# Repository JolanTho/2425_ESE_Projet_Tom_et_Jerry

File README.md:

# 2425_ESE_Tom&Jerry

## Sommaire
- [Présentation](#présentation)
- [Mécanique](#1-mécanique)
- [Électronique](#2-électronique)
- [Informatique](#3-informatique)
- [Stratégies](#4-stratégies)
- [Installation](#installation)
- [Contribution](#contribution-)
- [Auteurs et Contact](#auteurs-)

---

## Présentation

>Bienvenue sur le dépôt GitHub de **Tom&Jerry**. Ce projet a pour but de développer un robot autonome qui sur un plan plat joue à chat. Le plan est sans rebord, les matchs de 60secondes et le robot change de rôle (Chat/Souris) lors des contacts avec le(s) autre(s) robot(s).

>Ce projet est organisé en trois sous-domaines principaux :
>* **Mécanique** : Conception et fabrication des structures et composants mécaniques.
>* **Électronique** : Conception des circuits électroniques et sélection des composants.
>* **Informatique** : Développement du logiciel et de l'algorithme pour le contrôle du système.
>* **Stratégies** : Focus sur les stratégies mises en place pour s'échapper ou capturer.

---

## Détails du Projet

### 1. Mécanique
>Cette section est dédiée à la conception et à la fabrication des parties mécaniques du projet. 

#### Description :
- **Modélisation CAO** : Les pièces du projet ont été modélisées en utilisant **OnShape**.
- **Matériaux** : Les matériaux utilisés incluent **Plastique PLA, ...**.
- **Assemblage** : Le système est assemblé à l’aide de **(ex. vis, écrous, etc.)** et monté selon les plans fournis dans le dossier **/mechanical_drawings**.

#### Fichiers et Dossiers :
>* **/mechanical_drawings/** : Contient les fichiers CAO et les plans techniques.
>* **/materials_list.txt** : Liste des matériaux et composants utilisés.

---

### 2. Électronique
>Cette partie couvre la conception et le développement des circuits électroniques nécessaires pour alimenter et contrôler le système.

#### Description :
>* **Schémas électroniques** : Conception des circuits avec **Kicad**.
>* **Liste des composants** : Utilisation de microcontrôleurs comme **STM32**, capteurs **TOF, Capteur fin de course, Lidar, IMU, Odom**, et actionneurs **Moteurs de roues**.
>* **PCB** : Un circuit imprimé (PCB) a été conçu pour **Alimentation & Décision du robot**.

#### Fichiers et Dossiers :
>* **electronique/Tom&Jerry_PCB/** : Projet Kicad du PCB principal.
>* **electronique/TOF_PCb/** : Projet Kicad du PCB annexe pour les TOF.
>* **[Read.me ToF](electronique/READMETom&Jerry.md)**
>* **[Read.me Tom&Jerry](electronique/READMETom&Jerry.md)**

---

### 3. Informatique
>Cette section inclut le code source et les algorithmes permettant de contrôler le système.  

#### Description :
>* **Langages utilisés** : Le logiciel a été développé en **C**.  
>* **Architecture logicielle** : L'architecture du programme suit un modèle **/programm_diagramm**.  
>* **Modules et fonctionnalités** : Le logiciel gère **(ex. les capteurs, la communication avec le microcontrôleur, les algorithmes de contrôle**.  

#### Fichiers et Dossiers :
>* **/src/** : Contient le code source du projet.  
>* **/docs/** : Documentation du code et guide d’utilisation.  
>* **/scripts/** : Scripts auxiliaires pour tester ou déployer le logiciel.  
>* **[Read.me](software/README.md)**
---

### 4. Stratégies
>Cette section inclut tout ce qu'il faut savoir sur les stratégies décidées et mis en oeuvre.  

>[!Note]
> Pour faire fonctionner le robot plusieurs stratégies peuvent être mises en place.   
> **Lorsque nous sommes souris**  
>* 1. On fait avancer le robot sur des stratégies prédéfinies et on espère ne pas tomber sur le chat.  
>* 2. On donne des trajectoires aléatoires au robot et on espère ne pas tomber sur le chat ou de la table.  
>* 3. On donne des trajectoires aléatoires en évitant le chat en priant pour ne pas tomber de la table.  
>* 4. On utilise un champ de potentiel pour se repérer et éviter le chat et les bordures.  
>  
> **Lorsque nous sommes Chat**  
>* 1. On fait avancer le robot sur des stratégies prédéfinies et on espère toucher une souris.   
>* 2. On donne des trajectoires aléatoires au robot et on espère toucher une souris sans tomber.  
>* 3. Le Lidar donne l'endroit ou on fonce a pleine balle.  
>* 4. Le lidar donne l'endroit ou on fonce a pleine balle en prenant en compte que l'objectif bouge.   

---

## Installation

### Prérequis :
>[!Important]
>* **Matériel** : La liste du matériel nécessaire ce situe dans le fichier BOM ici, ainsi que dans la partie mécanique ici.
>* **Logiciel** : Nous utilisons STM32 CubeIDE pour programmer notre microcontrolleur. De plus pour la simulation le python est utilisé. 
>* **Connaissance** : Pour comprendre plainement le projet il est nécessaire de maitriser (Kicad, STM32CubeIDE, Onshape). Avec une idée de comment marche les microcontrolleur STM32. (Un ensearque a réussi vous devriez aussi y parvenir).

---

### Instructions :

>[!Tip]
> **Pour utiliser le projet sur un robot**  

1. Cloner le dépôt : 
   ```bash
   git clone https://github.com/JolanTho/2425_ESE_Projet_Tom_et_Jerry.git
   cd projet
   
>[!Tip]
> **Pour utiliser la simulation de champs potentiel**  

1. Cloner le dépôt : 
   ```bash
   git clone https://github.com/JolanTho/2425_ESE_Projet_Tom_et_Jerry.git
   cd projet
---

## Contribution :

---

## Auteurs : 
>* Jolan Thomasset (jolan.thomasset@ensea.fr)  
>* Romain Pace   (romain.pace@ensea.fr)  
>* Rémi Weidle   (remi.weidle@ensea.fr)

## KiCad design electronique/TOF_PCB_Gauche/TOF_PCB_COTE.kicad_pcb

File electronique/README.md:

# Partie éléctronique 

## Sommaire
- [Présentation](#présentation)
- [Alimentation](#alimentation)
- [Driver Moteurs](#drivers-moteurs)
- [STM32](#stm32)
- [Peripheriques](#périphériques)
- [Peripherique Annexe](#périphériques-annexes)
- [Musique](#musique)

---

## Présentation
>Bienvenue dans la partie éléctronique du projet, dans ce dossier sont présent tous les fichiers de conception du PCB KiCad ainsi que tous les fichiers de fabrications Gerber.  
Deux fichiers sont actuellement dans le directory. Tom&Jerry_PCB pour le PCB principal et TOF_PCB pour le secondaire.   
Il est détaillé chaque composante du Schématique/PCb dans ce Read.me  

---

## Alimentation
>[!Tip]
>Pour notre robot nous utilisons plusieurs système pour gérer le circuit d'alimentation. On a entre autre un BMS ( Batterie système management ), ainsi qu'un pseudo Power Path Management. La batterie utilisée est la suivante : [here](../datasheet/Batterie.pdf)  

>[!Tip]
>Des connecteurs Pac-Man sont utilisés au niveau de la recharge de batterie afin de pouvoir déconnecter facilement le circuit de charge si il est foireux. De plus un interrupteur est ajouté pour allumer/Eteindre le robot ainsi qu'un fusible pour protéger des surcourants sur la batterie.  

**Recharge de batterie**

[Recharge](../screenshot/electronique/usbC.png)

>Pour la recharge de la batterie nous prévoyons deux connecteurs : Type-C et Bornier afin de pouvoir recharger la batterie par alimentation stabilisée de labo ainsi que par cable USB-C (Plus difficile à mettre en oeuvre) [Documentation1](../datasheet/PPM_BMS.pdf).  

>[!Note]
>Cette entrée d'energie est gérée par le **BMS [BQ25172DSGR](../datasheet/BQ25172.pdf) de TI**. Celui-ci est cablé tel quel :  
>* IN : Entrée de tension de charge de batterie. Max 0.8 A (Cf : Doc)  
>* VSET : Programme le nombre de cellule --> 6 cellules + Charge intermittente  
>* ISET : Programme le courant de charge --> 0.8A   
>* TMR : Programme le Timer de sureté --> 6Hr  
>* TS : Programme la température de sureté de charge --> Donnée constructeur    
>* OUT : Sortie de tension de charge de la batterie  
>* STAT : Sortie d'indication de l'état de charge à drain ouvert  
>* EXP : Ground (Pad thermique)  
>* GND : Ground  

[CanalP](../screenshot/electronique/canalP.png)

>On a un transistor à canal P pour bloquer la charge du circuit par batterie lorsqu'une tension vient du bornier ou de l'USB-C. De plus on ajoute des condensateur (C...) pour eviter les retours de courant dû a des freinage des roues dans la résistance et donc dans l'alimentation derrière [(Doc)](../datasheet/slua376.pdf).    

>On utilise un premier convertisseur Buck pour abaisser la tension à 5V. Celui-ci est à découpage donc plus cher mais possède un meilleur rendement et un plus faible échauffement. Cela est parfait puisqu'il alimente le lidar ainsi que tous les circuits 3.3v derrière et donc peut avoir des appels de courant assez élevé (Comme démarrage de lidar).  

>[!Note]
>**Convertisseur Buck ([MP1475](../datasheet/MP1475.pdf))**  
>* IN : Tension d'entrée  
>* BST : Bootstrap  
>* SWT : Sortie de commutation  
>* PG : Sortie de puissance  
>* VCC : LDO interne de 5v  
>* EN/SYNC : Pour les clocks externes  
>* FB : Feedback  
>* GND : Ground  

>Actuellement les données sont celle ce la doc. La seule chose réglée est le pont diviseur avec une Vref = 1.25V pour avoir une sortie de 5V en sortie.  

>Simple convertisseur linéaire qui abaisse de 5V vers 3.3V pour alimenter certains capteurs ou encore la STM32 qui n'accepte pas du 5V. L'utilisation d'un buck serai plus utile si on recherche la performance cependant un LDO est suffisant car moins couteux, plus simple à mettre en place. L'abaissement de tension est faible sur de faible courants par conséquent la dissipation thermique sera faible ce qui justifie un LDO plutôt qu'un buck.  

>[!Note]
>**Convertisseur LDO [(BU33SD5WG-TR)](../datasheet/buxxsd5wg-e.pdf)**  
>* VIN : Tension d'entrée  
>* GND : Ground  
>* STBY : StandBy --> Ici sur High il marche dés qu'il est alimenté.   
>* N. C. : No Connected pin  
>* Vout : Tension de sortie  

---

## Drivers moteurs
>Afin de pouvoir mouvoir le robot sur la table de jeu, nous utilisons des moteurs type MCC (DfRobot FIT0520). Ces moteurs possèdent des codeurs déjà sur l'arbre moteur ce qui a l'avantage de ne négliger aucun décalage entre une roue de codeur et la roue de l'arbre moteur. Cependant si jamais la roue patine ou glisse le codeur ne prendra pas en compte ce dérapage ce qui entrainera des erreurs. Il faut donc impérativement que la mécanique permette au robot de rester particulièrement stabilisé sur le sol.  

>[!Note]
>Branché sur la carte les deux moteurs auront de beaux JST-XH de 6 Pins chacun tels que :  
>* Motor - : Phase - du moteur  
>* Motor + : Phase + du moteur  
>* GND : Ground   
>* 5V : Alimentation des codeurs en 5V   
>* Codeur PH1 : Pin allant avec PH2 avec la trame du codeur pour déterminer ensuite la vitesse du robot.   
>* Codeur PH2 : Pin allant avec PH1 avec la trame du codeur pour déterminer ensuite la vitesse du robot.   

>Pour controler ces deux moteurs chaque moteur aura son driver.   

>[!Note]
>**Driver [ZXBM5210](../datasheet/ZXBM5210.pdf)**  
>* Vref : Tension de référence pour setup l'oscillator PWM du composant.   
>* VDD : Alimentation du composant en 5V   
>* VM : Tension d'alimentation des moteurs  
>* FWD : PWM pour faire avancer le robot  
>* REV : PWM pour faire reculer le robot  
>* Out 1 :  Sortie au moteur phase -  
>* Out 2 : Sortie au moteur phase +  

>[!Important]
>Il est à noter que des capa de découplage sont utilisés afin d'éviter les fluctuation de courant trop rapide sur Vref ( Car tension de référence), sur les phases du moteur afin d'éviter des signaux créneau pur. De plus la documentation suggère un système de diode afin d'éviter la réversibilité du courant vers la batterie. Celui-ci ne sera pas utilisé afin d'éviter de cramer des diodes suite à des quantités trop importantes de courant que se déchargeraient dans les diodes.   

>[!Tip]
>En plus de cela nous utilisons un composant pour mesurer le courant drainé de la batterie vers les moteurs à l'aide d'une résistance dite shunt. Ce composant permettra de nous aider à asservir pourquoi pas en courant mais aussi de protection afin d'éviter comme nous n'avons pas mis les diodes d'avoir des données sur ce qui se passe.  

>[!Note]
>**Mesureur de courant [NCS199A2RSQT2G](../datasheet/NCS199A2RSQT2G.pdf)**  
>* GND : Ground  
>* In + : Entrée + coté résistance de shunt pour capter le courant  
>* In - : Entrée - coté résistance de shunt pour capter le courant  
>* Vs : Tension d'alimentation du composant  
>* Vref : Tension de référence dont je ne sais pas à quoi elle sert (J'ai cable comme la doc)  
>* Out : Sortie du composant avec ke courant prêt à être lu par un ADC  

>Comme toute entrée de composant celui-ci ne fait pas l'impasse une capacité de découplage a été ajoutée. De plus la résistance de 1kOhm a été mise pour préparer l'entrée du courant dans l'ADC conforme à la documentation.  

---

## STM32 
>[!Important]
>Avant de développer sur la STM32 et la facon dont nous avons répartis les pins de celle-ci. Pour que celle-ci fonctionne correctement nous utiliserons un quartz externe pour cadencer la STM32 (Configuré dans l'IOC de STM32CubeIDE). 

>[!Important]
>De plus nous utilisons une connexion STLink pour le debug de la carte via PC. 

---

## Périphériques 

>[!Note]
>La carte actuelle va gérer certains capteurs. Avec ceux-ci le robot pourra (Nous l'esperons) se repérer sur la table et réaliser au mieux la stratégie mise en place. 

>[!Tip]
> Afin de détecter les bords nous avons décider de faire de la redondance. En effet nous utilisons des capteurs "Moustache" ainsi que TOF pour repérer les bords de la table et éviter que les robots tombent. L'avantage des capteurs moustache est qu'ils sont mécanique donc fiable maintenant cela demande de na pas louper son intégration sur la base roulante ce qui n'es tpas gagner. Pour cela nous pouvvons utiliser les TOF. Ceux-ci sont plus simple à positionner sur le robot et à fonctionner. Cependant l'exploitation des données est plus dure (I2C + GPIO Extender...). 

>[!Note]
>Branché sur la carte les quatre capteurs moustahce ont un JST  :  
>* 3.3V : Alimentation
>* GND : Ground  
>Ceux-ci marchent en interrupteur pas besoin de plus de chose pour lire leurs données. 

>[!Note]
>**Capteurs TOF [VL53L1X](../datasheet/VL53L1X.pdf):**   
>* AVDDVCSEL : VCSEL tension d'alimentation  
>* AVSSVCSEL : VCSEL Ground    
>* GND1 - GND4 : Ground  
>* XShut: Pin pour shutdown le composant. celui-ci est actif sur un signal Bas  
>* GPIO1 : GPIO pour gérer les interruptions  
>* DNC : A ne pas connecter (Doit être floating)  
>* SDA : Serial data bus
>* SCL : Serial clock bus
>* AVDD : Tension d'alim du composant
>Ceux-ci sont sur les cartes fournient avec produit par STM32. 

>[!Note]
>En plus de la détection de bord avec les TOF et les capteurs "Moustache", le robot aura un IMU pour faire de la fusion de donnée (Rédigé en septembre ca ne sera pas traité pas assez de temps) ainsi que de vérifier si un robot nous touche. De plus il y aura un lidar pour détecter les robots sur la table et foncer sur eux. 

>[!Note]
>**Capteurs TOF [YDLidar X2](../datasheet/YDLIDARX2.pdf):**    
>* M_CTR : Entrée de la PWM du moteur du Lidar    
>* TX : Sortie UART avec les données du LIDAR      
>* GND : Ground    
>* VCC : Tension d'alimentation du lidar (5v)  

>[!Note]
>**IMU [ADXL343](../datasheet/ADXL343.pdf):**   
>* Vs : Tension d'alimentation du composant   
>* GND : Ground   
>* VDD : Tension d'alimentation de l'interface digitale  
>* SDA : Serial data bus  
>* SCL : Serial clock bus  
>* SDO : I2C adresse  
>* NC : A garder non connecte  
>* Int1 - Int2 : Pin d'interruption   
>* CS : Chip Select

---

## Périphériques Annexes 
>Deux composants non imposés ont été utilisés en plus de ceux imposés afin de pouvoir tout connecter à la STM32. Suite à la solution technique des TOF employé le nombre de GPIO recquis a quelque peu explosé surpassant la capacité de la STM. par conséquent un GPIO Extender est utilisé pour ajouter des GPIO afin de couper et utiliser les TOF lorsque nous en avons besoin.   

>[!Note]
>**GPIO Extender [TCA9555RTWR](../datasheet/TCA9555.pdf)**  
>* A0 : Adress Input 0  
>* A1 : Adress Input 1  
>* A2 : Adress Input 2  
>* GND : Ground   
>* P00 à P17 : P/port I/O connecte comme Input au démarrage.   
>* SCL : Serial clock bus  
>* SDA : Serial data bus  
>* VCC : Tension d'alimentation du composant  
>* INT : Permet de donner des interruptions avec une Pull-Up resistance.   

>[!Tip]
>En plus de ce composant nous avons utilisé un petit composant pour traiter nos leds. En effet en comptant 4 de débugs, robot allumé, chat/souris,... Nous nous sommes sentis à l'étroit et avons décidé de rajouter un composant qui drive 4 RGB. Cela sera parfait pour débug et montrer les informations nécessaires.  

>[!Note]
>**RGB LED Driver [LP5812CDSDR](../datasheet/LP5812.pdf)**  
>* VCC : Tension d'alimentation du composant  
>* GND : Ground  
>* SYNC : Synchro du composant sur GND (C'est la doc je sais pas pk)  
>* SCL : Serial clock bus  
>* SDA : Serial data bus   
>* OUT0 - OUT3 : Sorties vers les LED   

>Pour ce composant nous verrons pour le faire marcher en temps voulu avec le SPI pour allumer nos LEDS. Celles-ci sont cablés comme décrit dans la documentation.   

---

## Musique 
>Ayant dans notre groupe notre jolan nationnal, le projet ne pouvait être correctement réalisé sans l'ajout de bout de musique sur le robot. Pour se faire les sorties DAC de la STM32 dédiées seront utilisées. Ce signal audio sera amplifié par un amplificateur de Classe D puis va être envoyé dans des hauts parleurs.   

>[!Note]
>**Ampli de Classe D [PAM8302AAY](../datasheet/PAM8302A.pdf)**  
>* IN + : Entrée DAC  +  
>* IN - : Entrée DAC  -   
>* SD : Doit rester sur HIGh pour éviter qu'il soit shutdown (donc relié à 3.3v)  
>* VDD : Alimentation du composant  
>* OUT + : Sortie + du haut parleur   
>* OUT - : Sortie - du haut parleur  

>[!Important]
>Les deux capacité de découplage ainsi que les deux ferrites sont celles conforme à la documentation afin de réduire les interférence electromagnétique à partir de 1MHz et au dela. Ceci est parfait puisque ce composant est à coté de composant sensible comme la STM...  

## Auteurs : 
>* Jolan Thomasset (jolan.thomasset@ensea.fr)  
>* Romain Pace   (romain.pace@ensea.fr)  
>* Rémi Weidle   (remi.weidle@ensea.fr)

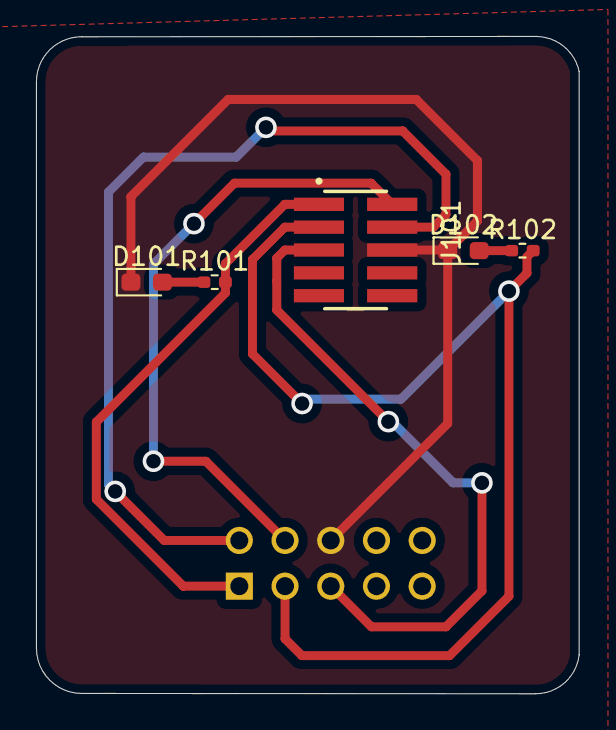
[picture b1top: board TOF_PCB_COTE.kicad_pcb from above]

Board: 2 copper layers, 30.2 x 36.5 mm, 6 parts (1 on the bottom side), 8 nets.

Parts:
D101, D102: LED; LED_0603_1608Metric_Pad1.05x0.95mm_HandSolder
J101: FTSH-105-01-F-DV-P-TR; SAMTEC_FTSH-105-01-F-DV-P-TR
R101, R102: 3.3k; R_0402_1005Metric_Pad0.72x0.64mm_HandSolder
U101: VL53L1X-SATEL; MODULE_VL53L1X-SATEL

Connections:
+5V: J101.05, U101.5 (VDD)
/I2C_MAIN_SCL: J101.04, U101.2 (SCL_I)
/I2C_MAIN_SDA: J101.02, U101.4 (SDA_I)
/TOF_GPIO1: J101.01, R101.2, U101.1 (INT_I)
/TOF_XSHUT: J101.03, R102.2, U101.3 (XSDN_I)
GND: D101.1 (K), D102.1 (K), J101.06, U101.6 (GND)
unnamed: D101.2 (A), R101.1
unnamed: D102.2 (A), R102.1

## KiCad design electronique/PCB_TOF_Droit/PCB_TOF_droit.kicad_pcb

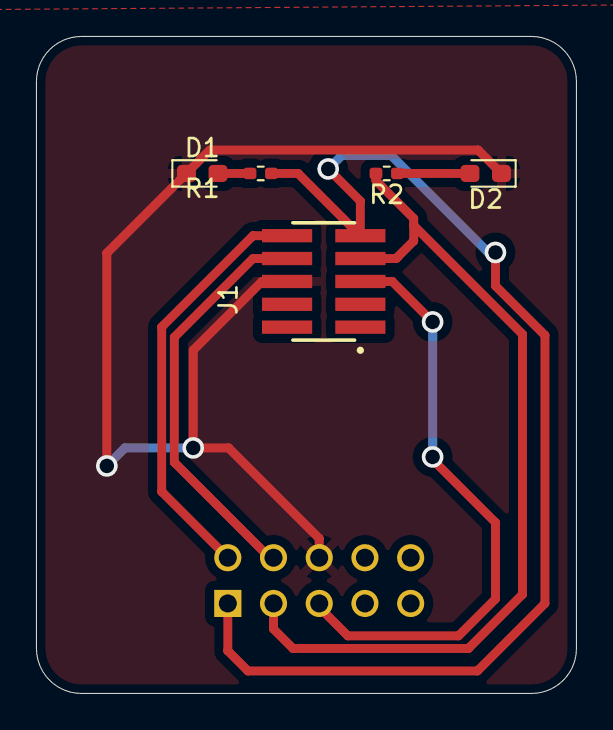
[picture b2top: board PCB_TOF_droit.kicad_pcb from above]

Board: 2 copper layers, 30.0 x 36.5 mm, 6 parts (1 on the bottom side), 8 nets.

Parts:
D1, D2: LED; LED_0603_1608Metric_Pad1.05x0.95mm_HandSolder
J1: FTSH-105-01-F-DV-P-TR; SAMTEC_FTSH-105-01-F-DV-P-TR
R1, R2: 3.3k; R_0402_1005Metric_Pad0.72x0.64mm_HandSolder
U1: VL53L1X-SATEL; MODULE_VL53L1X-SATEL

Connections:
+5V: J1.05, U1.5 (VDD)
/I2C_SCL: J1.10, U1.2 (SCL_I)
/I2C_SDA: J1.08, U1.4 (SDA_I)
/TOF_GPIO: J1.09, R1.2, U1.1 (INT_I)
/TOF_XSHUT: J1.07, R2.2, U1.3 (XSDN_I)
GND: D1.1 (K), D2.1 (K), J1.06, U1.6 (GND)
unnamed: D1.2 (A), R1.1
unnamed: D2.2 (A), R2.1

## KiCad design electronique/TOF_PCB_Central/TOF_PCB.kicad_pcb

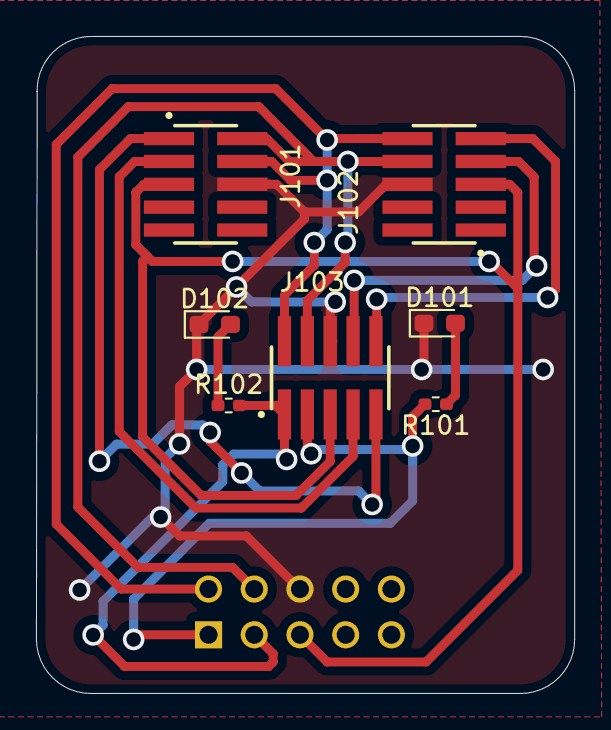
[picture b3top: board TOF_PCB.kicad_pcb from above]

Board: 2 copper layers, 29.9 x 36.5 mm, 8 parts (1 on the bottom side), 12 nets.

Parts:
D101, D102: LED; LED_0603_1608Metric_Pad1.05x0.95mm_HandSolder
J101, J102, J103: FTSH-105-01-F-DV-P-TR; SAMTEC_FTSH-105-01-F-DV-P-TR
R101, R102: 3.3k; R_0402_1005Metric_Pad0.72x0.64mm_HandSolder
U101: VL53L1X-SATEL; MODULE_VL53L1X-SATEL

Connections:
+5V: J101.05, J102.05, J103.05, U101.5 (VDD)
/I2C_MAIN_SCL: J101.04, J102.10, J103.02, U101.2 (SCL_I)
/I2C_MAIN_SDA: J101.02, J102.08, J103.04, U101.4 (SDA_I)
/TOFA_GPIO1: J103.03, R101.2, U101.1 (INT_I)
/TOFA_XSHUT: J103.01, R102.2, U101.3 (XSDN_I)
/TOFB_GPIO1: J101.01, J103.09
/TOFB_XSHUT: J101.03, J103.07
/TOFC_GPIO1: J102.09, J103.10
/TOFC_XSHUT: J102.07, J103.08
GND: D101.1 (K), D102.1 (K), J101.06, J102.06, J103.06, U101.6 (GND)
unnamed: D101.2 (A), R101.1
unnamed: D102.2 (A), R102.1

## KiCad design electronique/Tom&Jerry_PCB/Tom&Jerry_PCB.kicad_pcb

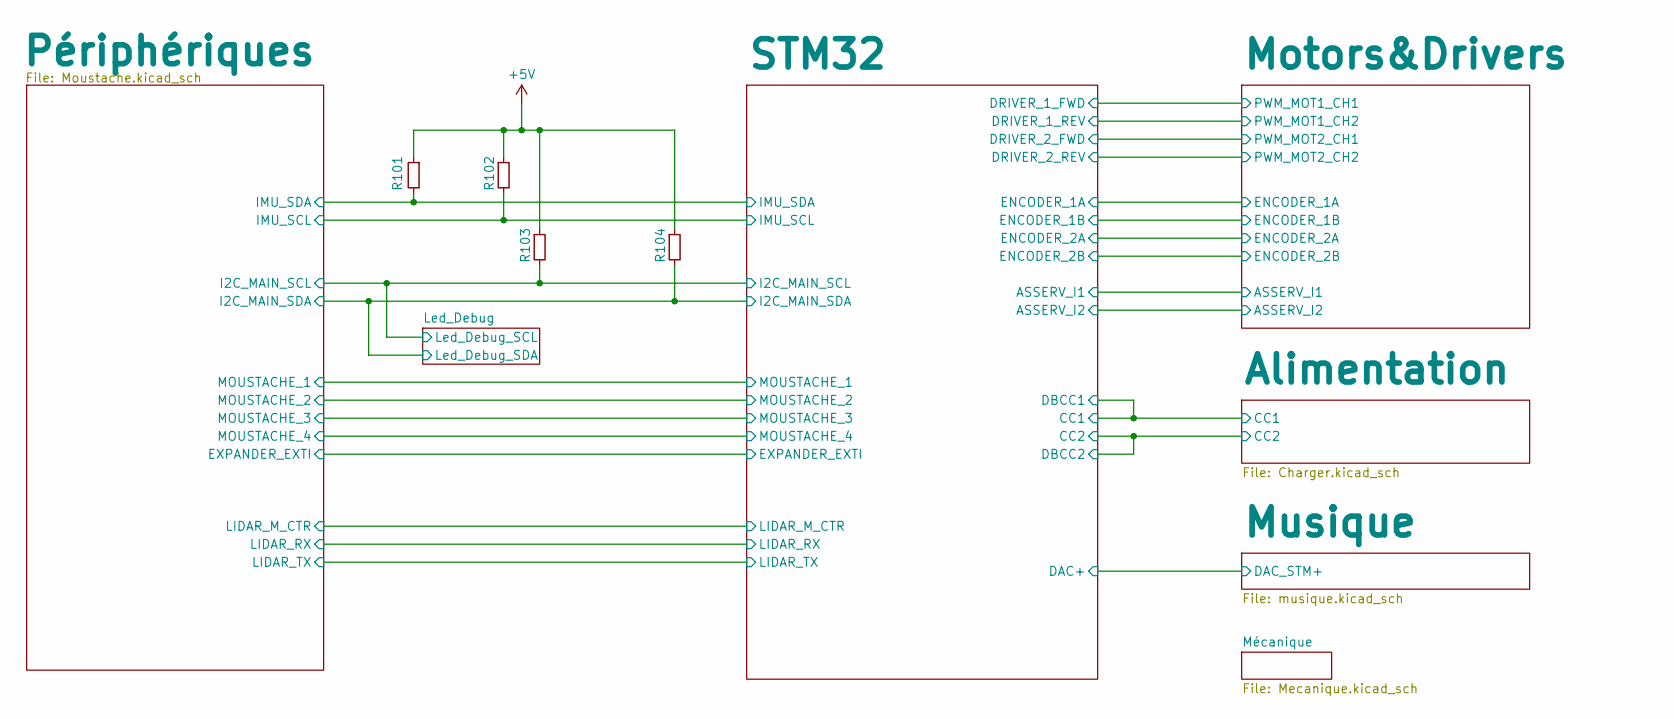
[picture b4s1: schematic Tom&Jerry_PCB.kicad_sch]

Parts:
R101, R102, R103, R104: 10k; R_0402_1005Metric

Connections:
+5V: R101.1, R102.1, R103.1, R104.1; also elsewhere on the board
/Led_Debug/Led_Debug_SCL: R103.2; also elsewhere on the board
/Led_Debug/Led_Debug_SDA: R104.2; also elsewhere on the board
/Périphériques/IMU_SCL: R102.2; also elsewhere on the board
/Périphériques/IMU_SDA: R101.2; also elsewhere on the board

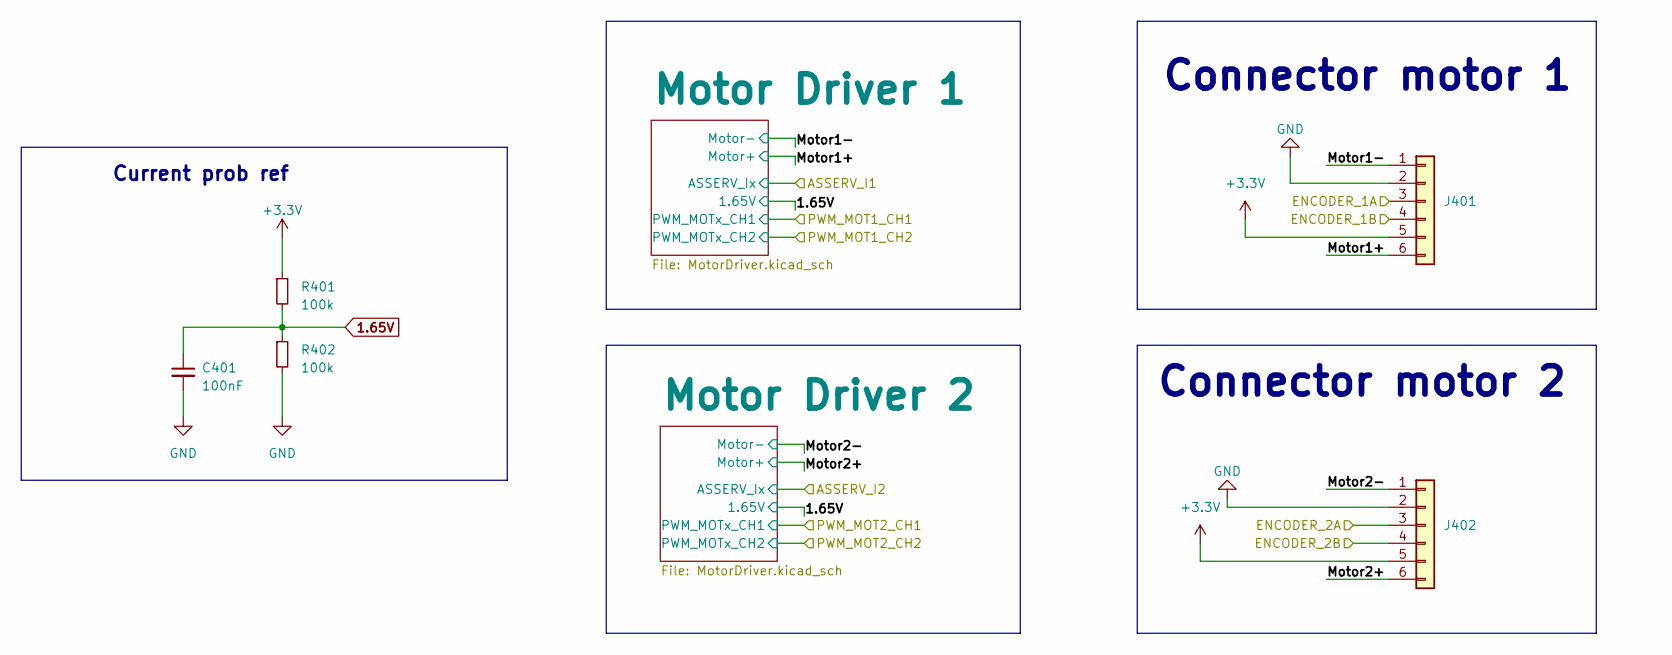
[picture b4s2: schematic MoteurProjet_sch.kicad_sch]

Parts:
C401: 100nF; C_0402_1005Metric
J401, J402: Conn_01x06; JST_XH_S6B-XH-A_1x06_P2.50mm_Horizontal
R401, R402: 100k; R_0402_1005Metric

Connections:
1.65V: C401.1, R401.2, R402.1; also elsewhere on the board
+3.3V: J401.5, J402.5, R401.1; also elsewhere on the board
/Motors&Drivers/ENCODER_1A: J401.3; also elsewhere on the board
/Motors&Drivers/ENCODER_1B: J401.4; also elsewhere on the board
/Motors&Drivers/ENCODER_2A: J402.3; also elsewhere on the board
/Motors&Drivers/ENCODER_2B: J402.4; also elsewhere on the board
/Motors&Drivers/Motor1+: J401.6; also elsewhere on the board
/Motors&Drivers/Motor1-: J401.1; also elsewhere on the board
/Motors&Drivers/Motor2+: J402.6; also elsewhere on the board
/Motors&Drivers/Motor2-: J402.1; also elsewhere on the board
GND: C401.2, J401.2, J402.2, R402.2; also elsewhere on the board

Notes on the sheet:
Current prob ref
Connector motor 1
Connector motor 2

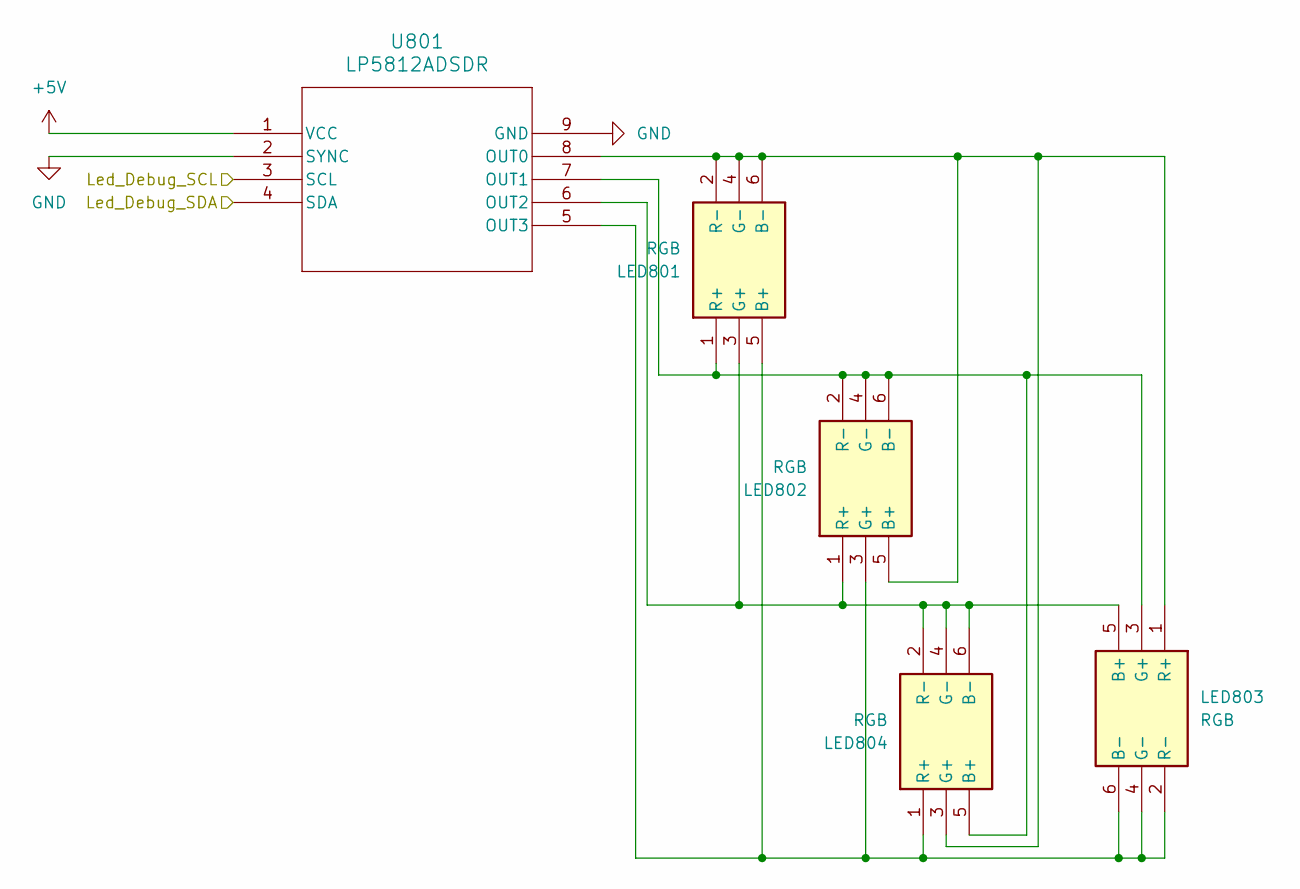
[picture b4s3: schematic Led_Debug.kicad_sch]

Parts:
LED801, LED802, LED803, LED804: RGB; 5988G10313F; Manufacturer_Part_Number 5988G10313F
U801: LP5812ADSDR; WSON8_DSD_TEX

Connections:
+5V: U801.1 (VCC); also elsewhere on the board
/Led_Debug/Led_Debug_SCL: U801.3 (SCL); also elsewhere on the board
/Led_Debug/Led_Debug_SDA: U801.4 (SDA); also elsewhere on the board
GND: U801.2 (SYNC), U801.9 (GND); also elsewhere on the board
unnamed: LED801.5 (B+), LED802.3 (G+), LED803.2 (R-), LED803.4 (G-), LED803.6 (B-), LED804.1 (R+), U801.5 (OUT3)
unnamed: LED801.2 (R-), LED801.4 (G-), LED801.6 (B-), LED802.5 (B+), LED803.1 (R+), LED804.3 (G+), U801.8 (OUT0)
unnamed: LED801.3 (G+), LED802.1 (R+), LED803.5 (B+), LED804.2 (R-), LED804.4 (G-), LED804.6 (B-), U801.6 (OUT2)
unnamed: LED801.1 (R+), LED802.2 (R-), LED802.4 (G-), LED802.6 (B-), LED803.3 (G+), LED804.5 (B+), U801.7 (OUT1)

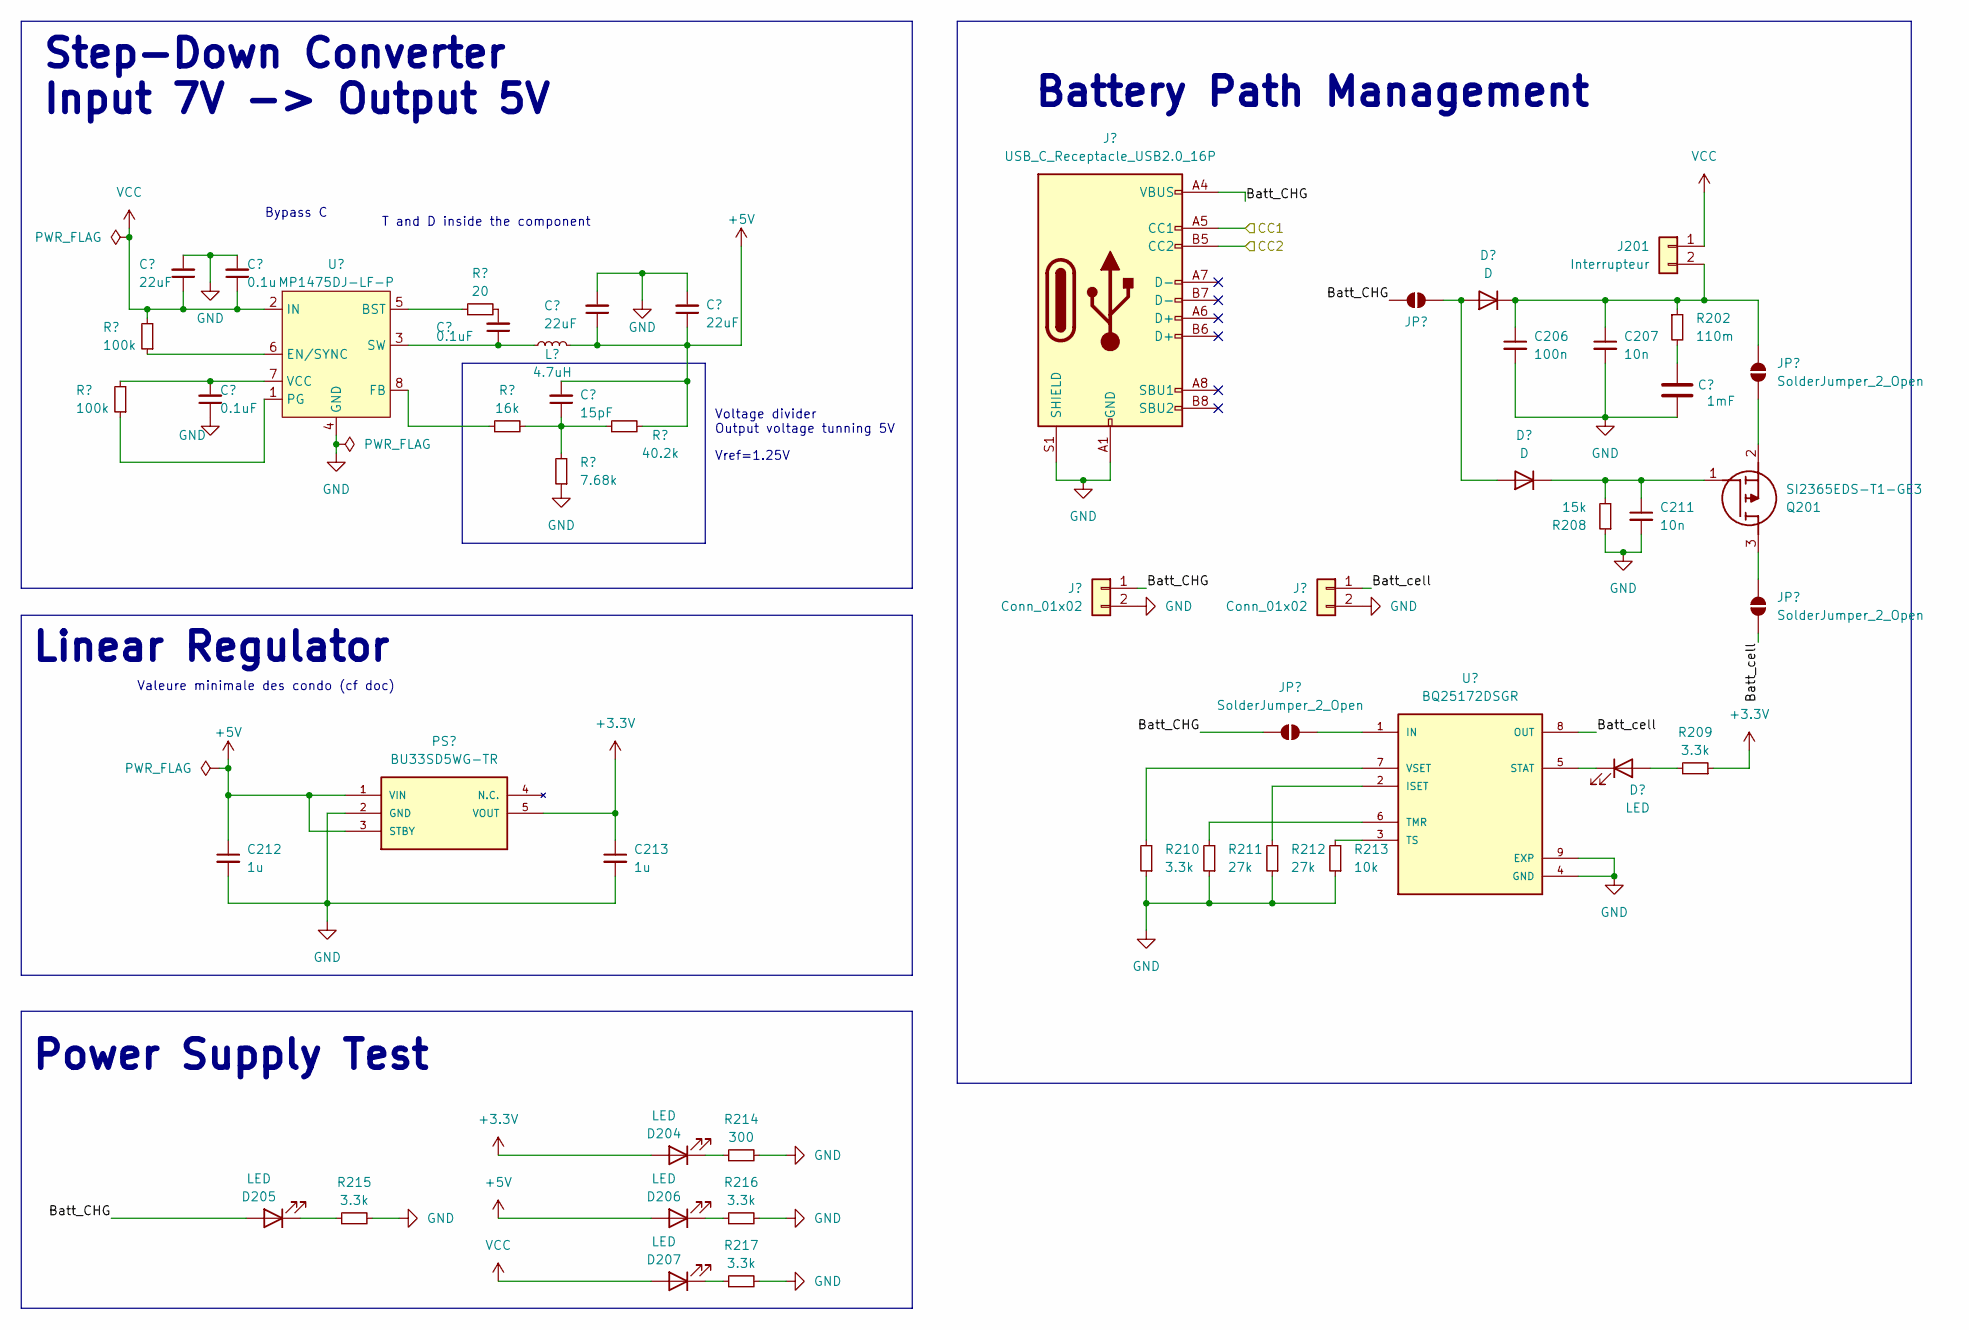
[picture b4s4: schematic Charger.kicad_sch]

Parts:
C201, C203, C204: 22uF; C_0805_2012Metric
C202: 0.1u; C_0402_1005Metric
C205, C209: 0.1uF; C_0402_1005Metric
C206: 100n; C_0402_1005Metric
C207, C211: 10n; C_0402_1005Metric
C208: 1mF; CAPAE1350X1400N
C210: 15pF; C_0402_1005Metric
C212, C213: 1u; C_0603_1608Metric
D201, D202: D; SODFL4825X110N
D203, D204, D205, D206, D207: LED; LED_0603_1608Metric_Pad1.05x0.95mm_HandSolder
J201: Interrupteur; Switch-3
J202: USB_C_Receptacle_USB2.0_16P; USB_C_Receptacle_HRO_TYPE-C-31-M-12
J203, J204: Conn_01x02; JST_XH_S2B-XH-A-1_1x02_P2.50mm_Horizontal
JP201, JP202, JP203, JP204: SolderJumper_2_Open; SolderJumper-2_P1.3mm_Open_TrianglePad1.0x1.5mm
L201: 4.7uH; L_0603_1608Metric_Pad1.05x0.95mm_HandSolder; Manufacturer_Part_Number 74438356047HT; Mouser Part Number 710-74438356047HT
PS201: BU33SD5WG-TR; SOT95P280X125-5N; Mouser_Part_Number 755-BU33SD5WG-TR
Q201: SI2365EDS-T1-GE3; SOT95P237X112-3N; Mouser Part Number 78-SI2365EDS-T1-GE3
R201: 20; R_0402_1005Metric
R202: 110m; R_0402_1005Metric
R203, R204: 100k; R_0402_1005Metric
R205: 16k; R_0402_1005Metric
R206: 40.2k; R_0402_1005Metric
R207: 7.68k; R_0402_1005Metric
R208: 15k; R_0402_1005Metric
R209, R210, R215, R216, R217: 3.3k; R_0402_1005Metric
R211, R212: 27k; R_0402_1005Metric
R213: 10k; R_0402_1005Metric
R214: 300; R_0402_1005Metric
U201: MP1475DJ-LF-P; SOT65P280X100-8N; Manufacturer_Part_Number MP1475DJ; Mouser Part Number 946-MP1475DJLFP
U202: BQ25172DSGR; IC_BQ25172DSGR; PARTREV June 2022

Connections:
+3.3V: C213.1, D204.2 (A), PS201.5 (VOUT), R209.1; also elsewhere on the board
+5V: C203.1, C204.1, C210.2, C212.1, D206.2 (A), L201.1, PS201.1 (VIN), PS201.3 (STBY), R206.2; also elsewhere on the board
/Alimentation/Batt_CHG: D205.2 (A), J202.A4 (VBUS), J202.A9 (VBUS), J202.B4 (VBUS), J202.B9 (VBUS), J203.1, JP201.1 (A), JP204.2 (B)
/Alimentation/Batt_cell: J204.1, JP203.1 (A), U202.8 (OUT)
/Alimentation/CC1: J202.A5 (CC1); also elsewhere on the board
/Alimentation/CC2: J202.B5 (CC2); also elsewhere on the board
GND: C201.2, C202.2, C203.2, C204.2, C206.2, C207.2, C208.2, C209.1, C211.2, C212.2, C213.2, J202.A1 (GND), J202.A12 (GND), J202.B1 (GND), J202.B12 (GND), J202.S1 (SHIELD), J203.2, J204.2, PS201.2 (GND), R207.1, R208.1, R210.1, R211.1, R212.1, R213.1, R214.2, R215.2, R216.2, R217.2, U201.4 (GND), U202.4 (GND), U202.9 (EXP); also elsewhere on the board
unnamed: C205.2, R201.2
unnamed: C208.1, R202.2
unnamed: C210.1, R205.2, R206.1, R207.2
unnamed: D201.2 (A), D202.2 (A), JP201.2 (B)
unnamed: C206.1, C207.1, D201.1 (K), J201.2, JP202.2 (B), R202.1
unnamed: C211.1, D202.1 (K), Q201.1 (G), R208.2
unnamed: D203.2 (A), R209.2
unnamed: D203.1 (K), U202.5 (STAT)
unnamed: D204.1 (K), R214.1
unnamed: D205.1 (K), R215.1
unnamed: D206.1 (K), R216.1
unnamed: D207.1 (K), R217.1
unnamed: JP202.1 (A), Q201.2 (S)
unnamed: JP203.2 (B), Q201.3 (D)
unnamed: JP204.1 (A), U202.1 (IN)
unnamed: R201.1, U201.5 (BST)
unnamed: R203.1, U201.6 (EN/SYNC)
unnamed: R205.1, U201.8 (FB)
unnamed: R204.1, U201.1 (PG)
unnamed: C205.1, L201.2, U201.3 (SW)
unnamed: C209.2, R204.2, U201.7 (VCC)
unnamed: R212.2, U202.2 (ISET)
unnamed: R211.2, U202.6 (TMR)
unnamed: R213.2, U202.3 (TS)
unnamed: R210.2, U202.7 (VSET)
VCC: C201.1, C202.1, D207.2 (A), J201.1, R203.2, U201.2 (IN); also elsewhere on the board

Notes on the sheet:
T and D inside the component
Valeure minimale des condo (cf doc)
Voltage divider Output voltage tunning 5V
Linear Regulator
Vref=1.25V
Step-Down Converter Input 7V -> Output 5V
Battery Path Management
Bypass C
Power Supply Test

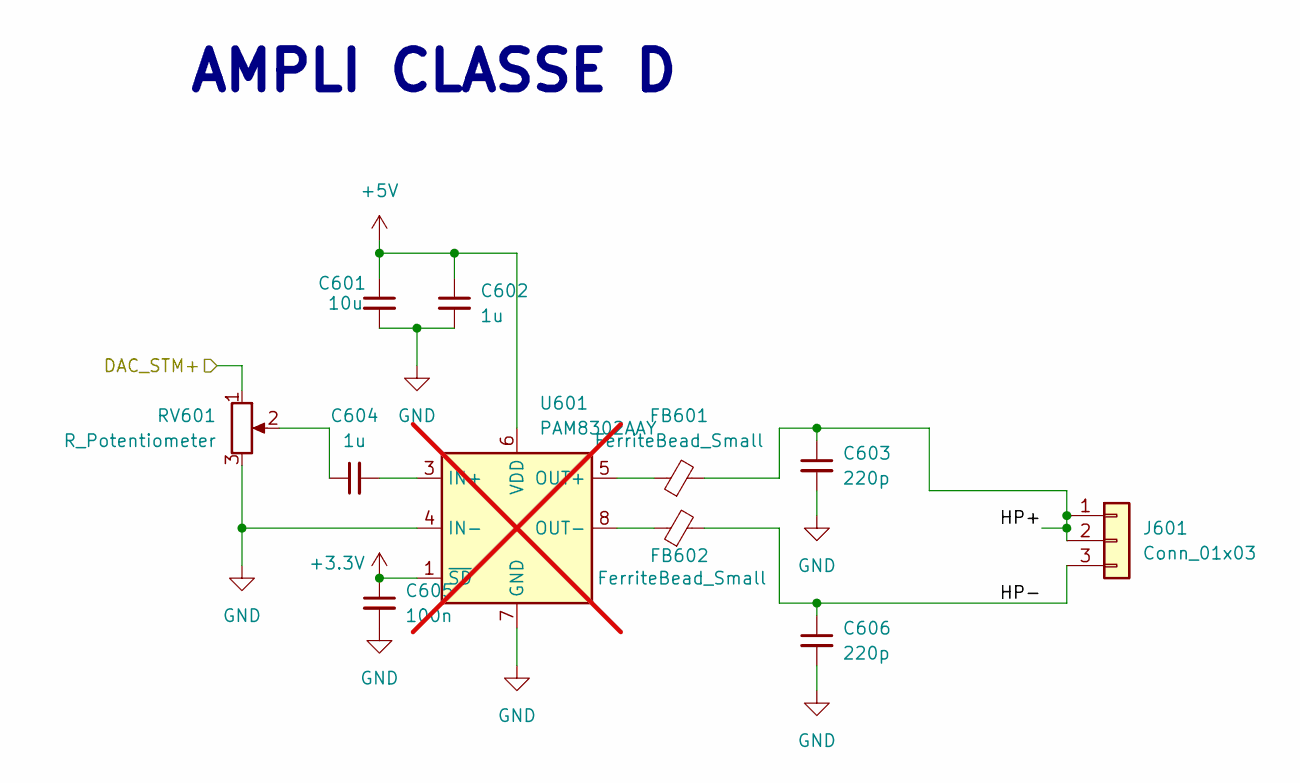
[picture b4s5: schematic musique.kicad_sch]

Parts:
C601: 10u; C_0603_1608Metric
C602, C604: 1u; C_0603_1608Metric
C603, C606: 220p; C_0402_1005Metric
C605: 100n; C_0402_1005Metric
FB601, FB602: FerriteBead_Small; L_0805_2012Metric
J601: Conn_01x03; JST_XH_S3B-XH-A_1x03_P2.50mm_Horizontal
RV601: R_Potentiometer; Potar
U601: PAM8302AAY; DFN300X300X80-8N; not fitted

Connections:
+3.3V: C605.1, U601.1 (~SD); also elsewhere on the board
+5V: C601.1, C602.1, U601.6 (VDD); also elsewhere on the board
/Musique/DAC_STM+: RV601.1; also elsewhere on the board
/Musique/HP+: C603.1, FB601.2, J601.1, J601.2
/Musique/HP-: C606.1, FB602.2, J601.3
GND: C601.2, C602.2, C603.2, C605.2, C606.2, RV601.3, U601.4 (IN-), U601.7 (GND); also elsewhere on the board
unnamed: C604.1, RV601.2
unnamed: C604.2, U601.3 (IN+)
unnamed: FB601.1, U601.5 (OUT+)
unnamed: FB602.1, U601.8 (OUT-)

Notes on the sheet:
AMPLI CLASSE D

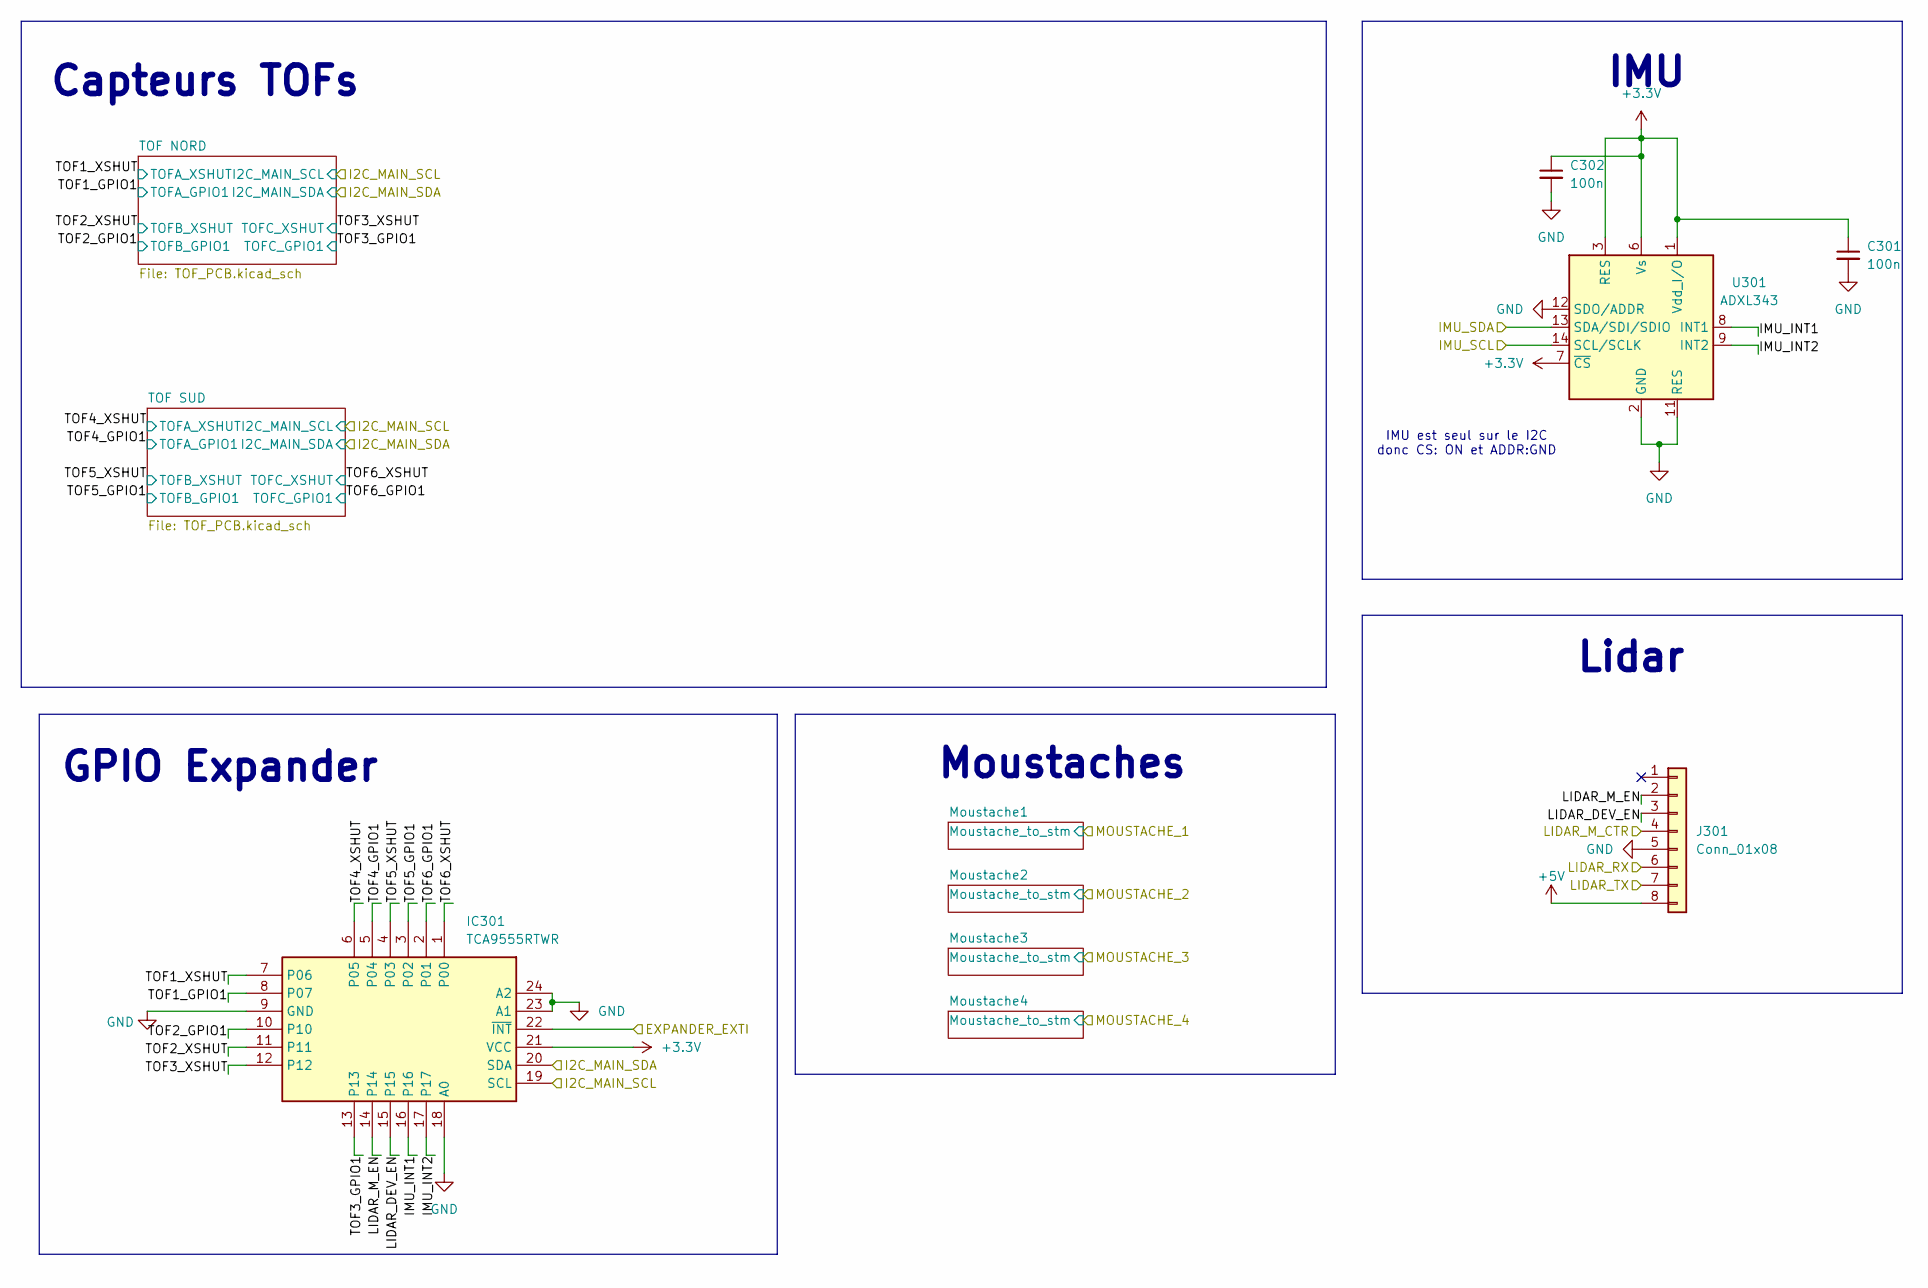
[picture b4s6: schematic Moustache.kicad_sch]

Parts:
C301: 100n; C_0402_1005Metric
C302: 100n; C_0603_1608Metric
IC301: TCA9555RTWR; RTW24_2P45X2P45; Manufacturer_Part_Number TCA9555RTWR; Mouser Part Number 595-TCA9555RTWR
J301: Conn_01x08; JST_XH_S8B-XH-A_1x08_P2.50mm_Horizontal
U301: ADXL343; PQFN80P300X500X100-14N

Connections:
+3.3V: C301.1, C302.1, IC301.21 (VCC), U301.1 (Vdd_I/O), U301.3 (RES), U301.6 (Vs), U301.7 (~CS); also elsewhere on the board
+5V: J301.8; also elsewhere on the board
/Led_Debug/Led_Debug_SCL: IC301.19 (SCL); also elsewhere on the board
/Led_Debug/Led_Debug_SDA: IC301.20 (SDA); also elsewhere on the board
/Périphériques/EXPANDER_EXTI: IC301.22 (~INT); also elsewhere on the board
/Périphériques/IMU_INT1: IC301.16, U301.8 (INT1)
/Périphériques/IMU_INT2: IC301.17, U301.9 (INT2)
/Périphériques/IMU_SCL: U301.14 (SCL/SCLK); also elsewhere on the board
/Périphériques/IMU_SDA: U301.13 (SDA/SDI/SDIO); also elsewhere on the board
/Périphériques/LIDAR_DEV_EN: IC301.15, J301.3
/Périphériques/LIDAR_M_CTR: J301.4; also elsewhere on the board
/Périphériques/LIDAR_M_EN: IC301.14, J301.2
/Périphériques/LIDAR_RX: J301.6; also elsewhere on the board
/Périphériques/LIDAR_TX: J301.7; also elsewhere on the board
/Périphériques/TOF1_GPIO1: IC301.8 (P07); also elsewhere on the board
/Périphériques/TOF1_XSHUT: IC301.7 (P06); also elsewhere on the board
/Périphériques/TOF2_GPIO1: IC301.10; also elsewhere on the board
/Périphériques/TOF2_XSHUT: IC301.11; also elsewhere on the board
/Périphériques/TOF3_GPIO1: IC301.13; also elsewhere on the board
/Périphériques/TOF3_XSHUT: IC301.12; also elsewhere on the board
/Périphériques/TOF4_GPIO1: IC301.5 (P04); also elsewhere on the board
/Périphériques/TOF4_XSHUT: IC301.6 (P05); also elsewhere on the board
/Périphériques/TOF5_GPIO1: IC301.3 (P02); also elsewhere on the board
/Périphériques/TOF5_XSHUT: IC301.4 (P03); also elsewhere on the board
/Périphériques/TOF6_GPIO1: IC301.2 (P01); also elsewhere on the board
/Périphériques/TOF6_XSHUT: IC301.1 (P00); also elsewhere on the board
GND: C301.2, C302.2, IC301.9 (GND), IC301.18 (A0), IC301.23 (A1), IC301.24 (A2), J301.5, U301.2 (GND), U301.4 (GND), U301.5 (GND), U301.11 (RES), U301.12 (SDO/ADDR); also elsewhere on the board

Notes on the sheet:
GPIO Expander
Moustaches
IMU
Lidar
IMU est seul sur le I2C donc CS: ON et ADDR:GND
Capteurs TOFs

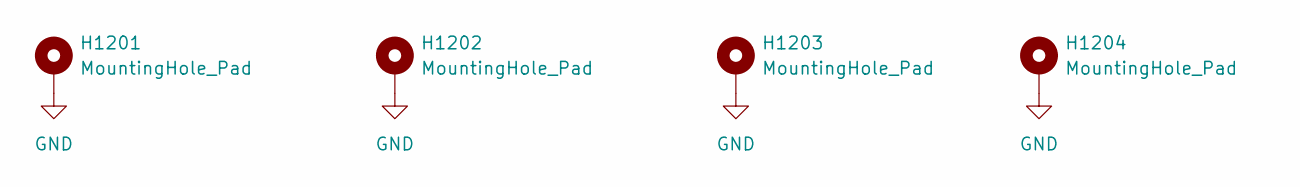
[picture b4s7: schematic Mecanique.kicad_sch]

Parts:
H1201, H1202, H1203, H1204: MountingHole_Pad; MountingHole_3.2mm_M3_Pad_Via

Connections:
GND: H1201.1, H1202.1, H1203.1, H1204.1; also elsewhere on the board
